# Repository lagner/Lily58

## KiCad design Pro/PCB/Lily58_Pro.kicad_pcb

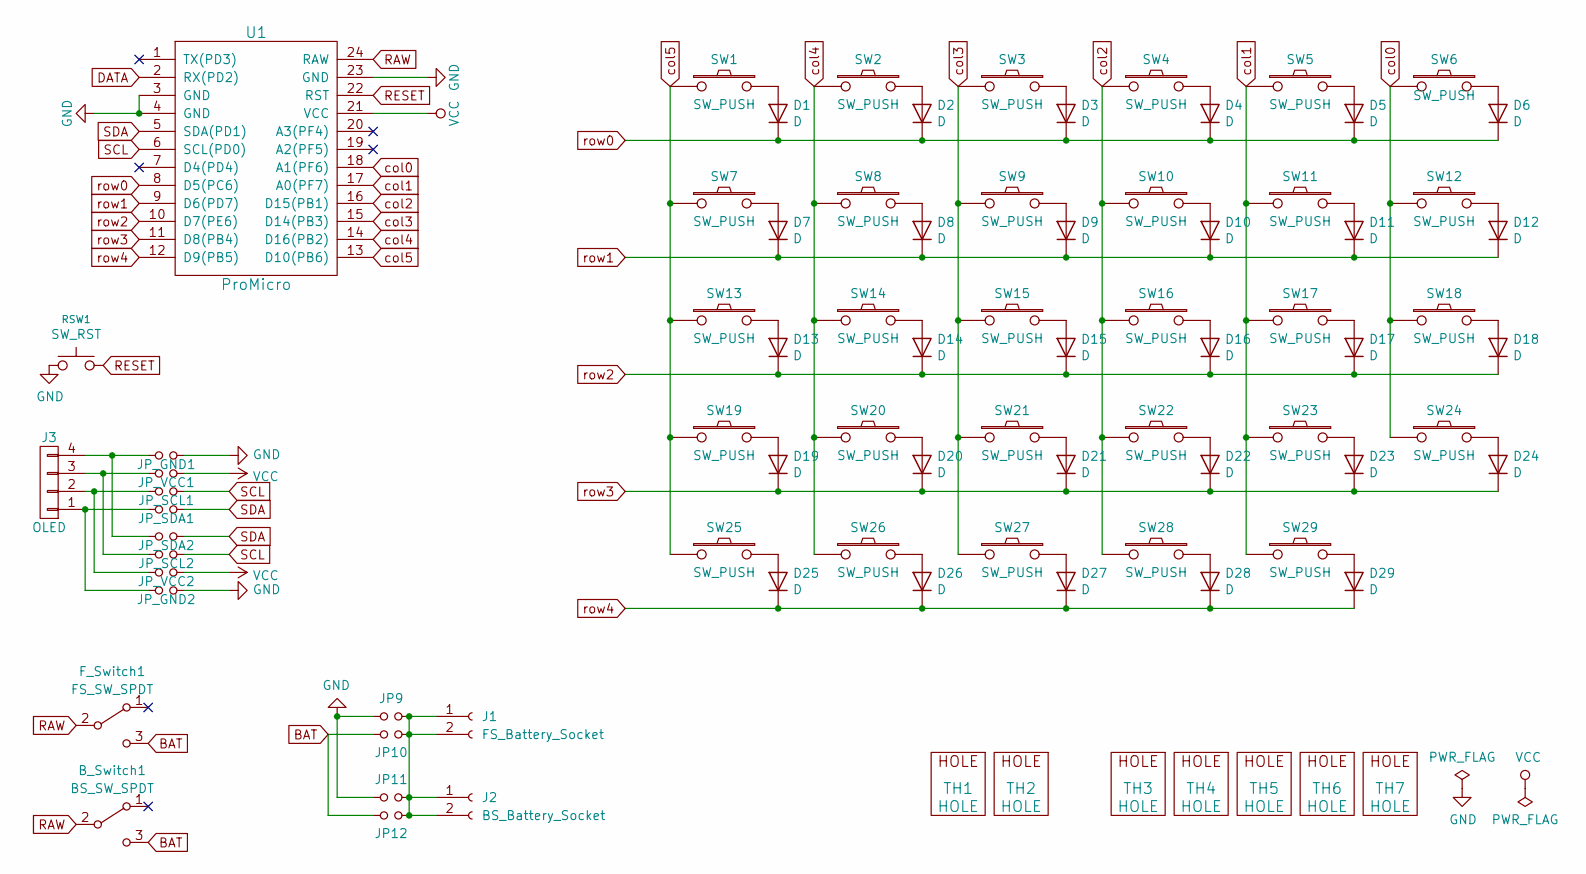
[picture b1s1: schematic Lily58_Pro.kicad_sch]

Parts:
B_Switch1: BS_SW_SPDT; SW_MSK12C02-HB
D1, D2, D3, D4, D5, D6, D7, D8, D9, D10, D11, D12, D13, D14, D15, D16, D17, D18, D19, D20, D21, D22, D23, D24, D25, D26, D27, D28, D29: D; Diode_SOD123
F_Switch1: FS_SW_SPDT; SW_MSK12C02-HB
J1: FS_Battery_Socket; JST_PH_S2B-PH-K_1x02_P2.00mm_Horizontal
J2: BS_Battery_Socket; JST_PH_S2B-PH-K_1x02_P2.00mm_Horizontal
J3: OLED; OLED_4Pin
JP9, JP10, JP11, JP12: Jumper
JP_GND1, JP_GND2: Jumper_NO_Small; Jumper
JP_SCL1, JP_SCL2: Jumper_NO_Small; Jumper
JP_SDA1, JP_SDA2: Jumper_NO_Small; Jumper
JP_VCC1, JP_VCC2: Jumper_NO_Small; Jumper
RSW1: SW_RST; TACT_SWITCH_TVBP06
SW1, SW2, SW3, SW4, SW5, SW6, SW7, SW8, SW9, SW10, SW11, SW12, SW13, SW14, SW15, SW16, SW17, SW18, SW19, SW20, SW21, SW22, SW23, SW24, SW25, SW26, SW27, SW28, SW29: SW_PUSH; MX_Choc_Hotswap
TH1, TH2: HOLE; HOLE_M2
TH3, TH4, TH5, TH6, TH7: HOLE; HOLE_M2_TH
U1: ProMicro; ProMicro_rev2

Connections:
BAT: B_Switch1.3 (C), F_Switch1.3 (C), JP10.1, JP12.1
DATA: U1.2 (RX(PD2))
GND: JP9.1, JP11.1, JP_GND1.2, JP_GND2.2, RSW1.1, U1.3 (GND), U1.4 (GND), U1.23 (GND)
unnamed: D1.2 (A), SW1.2
unnamed: D2.2 (A), SW2.2
unnamed: D3.2 (A), SW3.2
unnamed: D4.2 (A), SW4.2
unnamed: D5.2 (A), SW5.2
unnamed: D6.2 (A), SW6.2
unnamed: D7.2 (A), SW7.2
unnamed: D8.2 (A), SW8.2
unnamed: D9.2 (A), SW9.2
unnamed: D10.2 (A), SW10.2
unnamed: D11.2 (A), SW11.2
unnamed: D12.2 (A), SW12.2
unnamed: D13.2 (A), SW13.2
unnamed: D14.2 (A), SW14.2
unnamed: D15.2 (A), SW15.2
unnamed: D16.2 (A), SW16.2
unnamed: D17.2 (A), SW17.2
unnamed: D18.2 (A), SW18.2
unnamed: D19.2 (A), SW19.2
unnamed: D20.2 (A), SW20.2
unnamed: D21.2 (A), SW21.2
unnamed: D22.2 (A), SW22.2
unnamed: D23.2 (A), SW23.2
unnamed: D24.2 (A), SW24.2
unnamed: D25.2 (A), SW25.2
unnamed: D26.2 (A), SW26.2
unnamed: D27.2 (A), SW27.2
unnamed: D28.2 (A), SW28.2
unnamed: D29.2 (A), SW29.2
unnamed: J1.1, J1.2, J2.1, J2.2, JP9.2, JP10.2, JP11.2, JP12.2
unnamed: J3.1, JP_GND2.1, JP_SDA1.1
unnamed: J3.2, JP_SCL1.1, JP_VCC2.1
unnamed: J3.3, JP_SCL2.1, JP_VCC1.1
unnamed: J3.4, JP_GND1.1, JP_SDA2.1
RAW: B_Switch1.2 (B), F_Switch1.2 (B), U1.24 (RAW)
RESET: RSW1.2, U1.22 (RST)
SCL: JP_SCL1.2, JP_SCL2.2, U1.6 (SCL(PD0))
SDA: JP_SDA1.2, JP_SDA2.2, U1.5 (SDA(PD1))
VCC: JP_VCC1.2, JP_VCC2.2, U1.21 (VCC)
col0: SW6.1, SW12.1, SW18.1, SW24.1, U1.18 (A1(PF6))
col1: SW5.1, SW11.1, SW17.1, SW23.1, SW29.1, U1.17 (A0(PF7))
col2: SW4.1, SW10.1, SW16.1, SW22.1, SW28.1, U1.16 (D15(PB1))
col3: SW3.1, SW9.1, SW15.1, SW21.1, SW27.1, U1.15 (D14(PB3))
col4: SW2.1, SW8.1, SW14.1, SW20.1, SW26.1, U1.14 (D16(PB2))
col5: SW1.1, SW7.1, SW13.1, SW19.1, SW25.1, U1.13 (D10(PB6))
row0: D1.1 (K), D2.1 (K), D3.1 (K), D4.1 (K), D5.1 (K), D6.1 (K), U1.8 (D5(PC6))
row1: D7.1 (K), D8.1 (K), D9.1 (K), D10.1 (K), D11.1 (K), D12.1 (K), U1.9 (D6(PD7))
row2: D13.1 (K), D14.1 (K), D15.1 (K), D16.1 (K), D17.1 (K), D18.1 (K), U1.10 (D7(PE6))
row3: D19.1 (K), D20.1 (K), D21.1 (K), D22.1 (K), D23.1 (K), D24.1 (K), U1.11 (D8(PB4))
row4: D25.1 (K), D26.1 (K), D27.1 (K), D28.1 (K), D29.1 (K), U1.12 (D9(PB5))

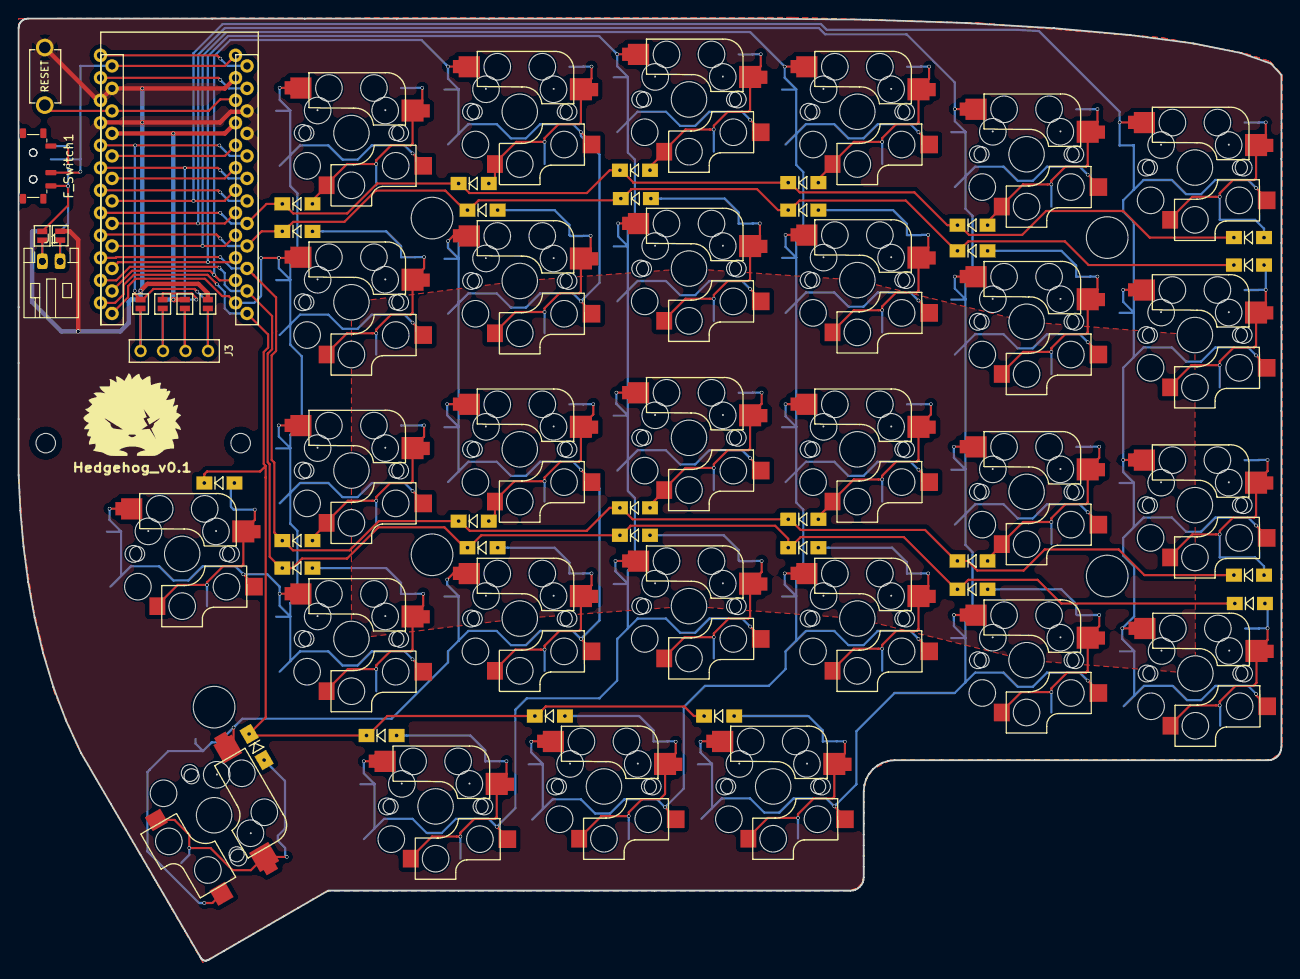
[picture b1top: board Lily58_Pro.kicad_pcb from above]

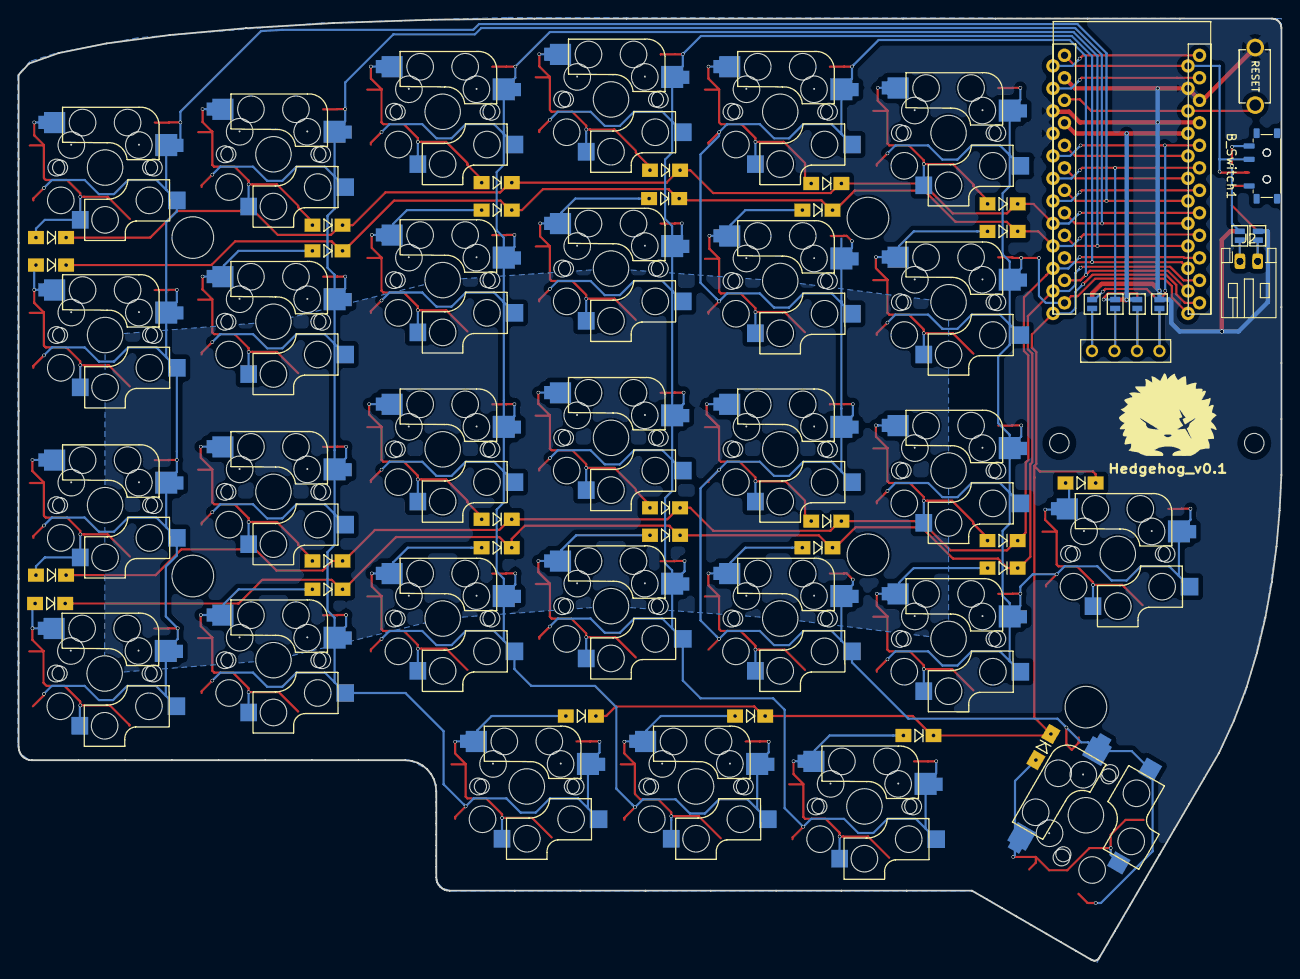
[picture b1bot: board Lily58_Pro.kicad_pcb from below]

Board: 2 copper layers, 142.5 x 106.3 mm, 86 parts (9 on the bottom side), 52 nets.

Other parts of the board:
Hedgehog_v0.1, Hedgehog_v0.1#2: LOGO; Hedgehog

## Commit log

2024-01-11 Add gitignore file
2024-01-11 Import project to Kicad 7
2024-01-11 Update project according KiCAD 7
2024-01-13 wireless scheme is almost ready
2024-01-13 Update gitignore
2024-01-13 Update Logo
2024-01-13 itermediate version
2024-01-13 It's done. v0.1 ready to print
